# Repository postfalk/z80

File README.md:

## Recent Bring-Up Notes

See [BASIC_DEBUG_2026-04-11.md](./BASIC_DEBUG_2026-04-11.md) for a summary of:

- BASIC workspace/RAM mapping fixes
- toolchain findings (`zasm` vs `z80asm`)
- UART and RAM smoke-test ROMs
- current diagnosis of the remaining BASIC startup issue

#My Z80 Computer

### Assembler software ####

There is a Z80 assembler in the Ubuntu universe repos!!!

```
sudo apt-get install z80asm 
```

Make sure z80asm is in your executable path. There is also a de-assembler for binaries (z80dasm).

I wrote a simple Python script to automate assembly.

```
python assemble.py -i test.asm
```

In order to review binary hex code install bless:

```
sudo apt-get install bless
```

Most software and examples are written in TASM, I found a compatible project still maintained called ZASM

http://k1.spdns.de/Develop/Projects/zasm/Distributions/

CPM setup

This page proved very useful

http://cpuville.com/cpm_on_new_computer.html

(Currently validating its usefulness)

------------- Much of the below is now obsolete ------------------

**Arduino driven Z80 development**

The Arduino is gone now. Development is fun without it. However, the form factor is still there. Arduino could be used for debugging as needed.

~~The basic idea of this project is to use an Arduino to support the development of a z80 computer system and debug any of its components in the process. The Arduino stands in as ...~~

~~a) reset generator~~
~~b) clock~~
~~c) ROM for the lowest 64byte 0000h-003Fh~~

~~The z80 code is fed from a C array to PORTD, PORTB (with 6pins on an Arduino UNO R3) as address bus, and PORTC simulates the control bus (RD --> PIN4, MRQ --> PIN2, RESET <-- PIN3, CLOCK <-- Pin5). The array index correspondends directly with the z80 system address.~~

~~The z80 board is more or less configured as an Arduino shield (even though bigger, the Arduino is plucked in upside down on top of it). In order to run the board without the Arduino, I created a circuit on an Arduino shield PCB with the reset and clock circuit. Thus, it is possible to go back and forth between normal computer operation and running debug code from Arduino.~~

~~The Arduino emulation runs somewhat over 600khz after stripping all pinMode routines out of the Arduino code. (I wonder whether the ```if ... else ...``` control structure could be replaced with bitwise logic as well).~~

~~After Arduino reset, the Aruino code will perform a z80 reset as well (which needs at least 4 clock cycles).~~

~~The clock speed can be modified by nserting Arduino delays in the code which is very useful for debugging. ```Serial.println``` ~~proved also very useful even though it might conflict with z80 data bus on PORT D. For this reason it needs to be placed strategically (e.g. at the high phase of the clock cycle).~~

A new idea is to use the Arduino as a simple IO device at the Z80 bus. At a 4Mhz clock it would require to use the WAIT signal.

***Prerequisites***

***EEPROM***

I got a very cheap, very universal EEPROM programmer called MiniPro TL866xx. It works perfectly with following project: 
Install the project if you want to use this project to directly write XPROMS with the code below.

https://github.com/vdudouyt/

Tested with [XICOR 28C64] (https://www.jameco.com/Jameco/Products/ProdDS/74827.pdf). The python code below assumes this 8k by 8byte device. Change code accordingly for other devices or more flexible use.

Example use:

````sh
minipro -p X28C64 -w d88_rom.bin
````

***RAM***

http://ee-classes.usc.edu/ee459/library/datasheets/628128.pdf

***Current configuration***

The circuit follows very closely http://www.z80.info/gfx/z80test.gif.

Differences: 

- I am using the more original ZILOG z80 PIO.

*Addresses*:

Memory:  

0000h - 003Fh   Arduino ROM emulation  
or  
0000h - 7FFFh   Space for ROM  
8000h - FFFFh   (static) RAM  

I/O:  

00h - 03h   PIO 
  00h         PORT A - ctrl  
  01h         PORT A - data  
  02h         PORT B - ctrl  
  03h         PORT B - data  
80h - 87h   UART - TL16C550A, documentation: http://www.pci-card.com/TL16C550.pdf

Using the 74HCT138 for address decoding we can address 8 devices (2 of the lines are still unused). The wiring is a little bit unusual here: A - A7, B - A6, C - A5

***Example code in this project***

*piobasics.asm*

Just turns bit 0 at port B on if addresses are configured as above. (any speed, originally 1 to 10hz :) )

*pioextended.asm*

Blinks bit 0 at port B if addresses are configured as above (optimized for, i.e. visible at 600kHz clock). Also requires RAM at ffffh for sub routine call. 

*d88.asm*

A somewhat unsuccessful attempt to drive a I2C 8x8 LED display from Adafruit. The program is able to output a "picture". However, the module used requires continous I2C clock which is hard to provide without timer interrupt. Might pick this project up once CTC interupts are available.

*serial.asm*

Basic implementation of a serial communixcation. Minimal working (output) setup using 9600-8-N-1 configuration:

To set the baud rate, we need to access the divisor registers, which is done by setting the most significant bit of the line control register to 1.

- set register 83 to 80 (1000 0000)

- now set dividers:
  
  * set register 80h to 0ch (12 for 9600)

  * set register 81h to 00h 

- now configure line control register

- set register 83h to 03h

- now transmit data by setting value of register 80h

- check register 85h bit 4 will tell whether transmission register is clear

*bootloader.asm*

- load file from serial port

- assembled code needs to start on 0800h

- file end is determined by time out

- jump to start program

*keyboard.asm*

- simple serial reflector of keyboard activity

- load with bootloader

***Documentation Links***

[Zilog User Manual] (http://www.z80.info/zip/z80cpu_um.pdf)

[CPM User Manual](http://www.cpm.z80.de/manuals/cpm3-usr.pdf)

###Explore

http://www.ecstaticlyrics.com/electronics/SPI/fast_z80_interface.html

[CPM 2.2 installation](http://cpuville.com/cpm_on_new_computer.html): This looks pretty reasonable. I like the idea to use an actual IDE hard disk and do not care about its compatibility outside the system. 

[http://www.glynstore.com/content/docs/ftdi/DS_VDIP2.pdf]: Explore this option to get USB sticks and FAT32 going relatively easily and somewhat lame.

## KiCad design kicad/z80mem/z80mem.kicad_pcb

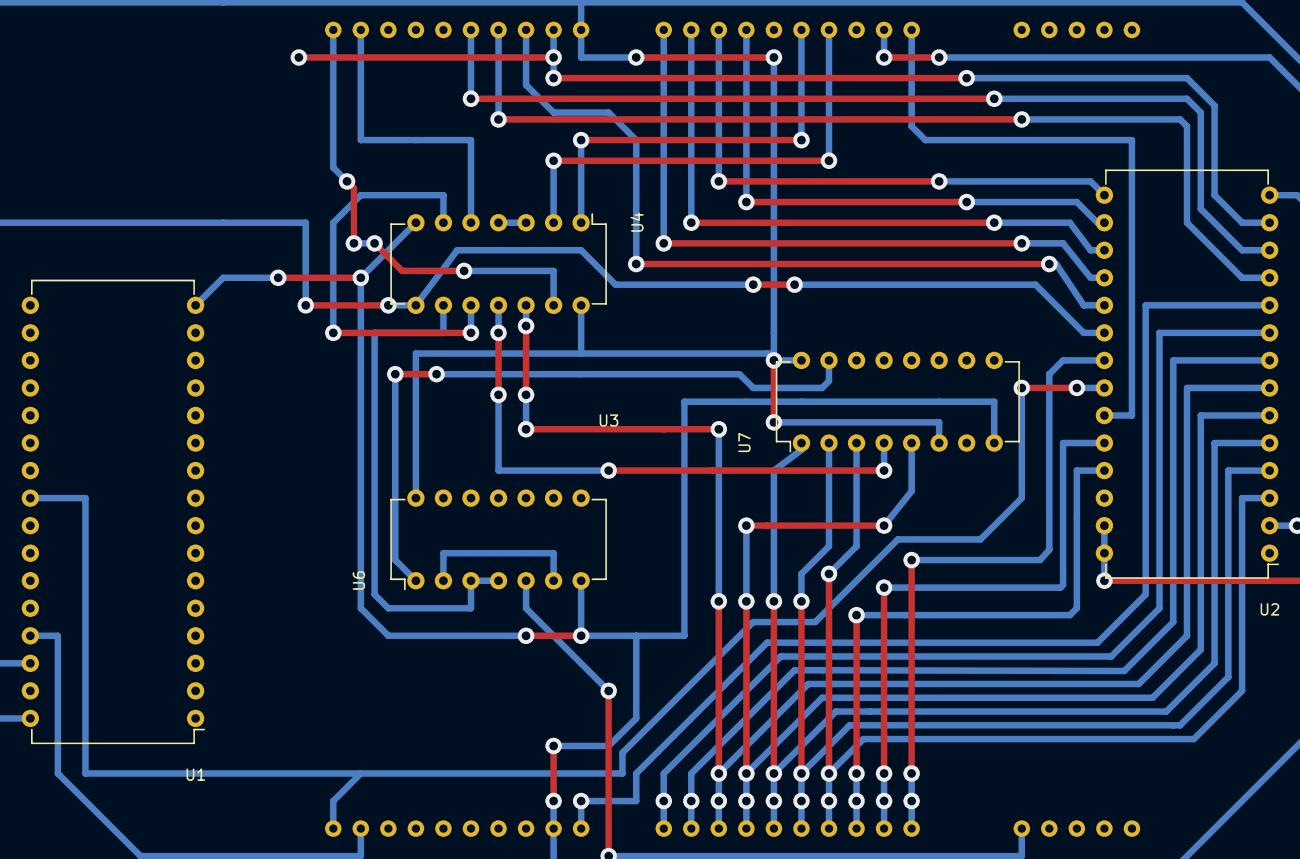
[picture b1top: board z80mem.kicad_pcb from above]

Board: 2 copper layers, 6 parts (0 on the bottom side), 37 nets.

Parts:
U1: MS628128; DIP-32_W15.24mm
U2: 2764; DIP-28_W15.24mm
U3: z80pcb; z80systemboard
U4: 74LS32; DIP-14_W7.62mm
U6: 7400; DIP-14_W7.62mm
U7: 74LS138; DIP-16_W7.62mm

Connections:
GND: U1.16, U2.14, U3.29, U4.7, U6.7, U7.8
unnamed: U1.30, U2.20, U4.8
unnamed: U4.3, U4.4
unnamed: U4.9, U6.3, U6.4
unnamed: U4.6, U4.10
unnamed: U4.11, U7.4
unnamed: U6.1, U7.15
unnamed: U6.2, U6.6
VCC: U1.32, U2.27, U2.28, U3.11, U4.14, U6.14, U7.6, U7.16
a0: U2.10, U3.30
a1: U2.9, U3.31
a2: U2.8, U3.32
a3: U2.7, U3.33, U4.12
a4: U2.6, U3.34, U7.5
a5: U2.5, U3.35, U7.1
a6: U2.4, U3.36, U7.2
a7: U2.3, U3.37, U7.3
a8: U2.25, U3.38
a9: U2.24, U3.39
a10: U2.21, U3.40
a11: U2.23, U3.1
a12: U2.2, U3.2
a14: U3.4, U4.2
a15: U3.5, U4.1
d0: U1.13, U2.11, U3.14
d1: U1.17, U2.12, U3.15
d2: U1.15, U2.13, U3.12
d3: U1.14, U2.15, U3.8
d4: U1.18, U2.16, U3.7
d5: U1.19, U2.17, U3.9
d6: U1.20, U2.18, U3.10
d7: U1.21, U2.19, U3.13
iorq: U3.20, U4.13
mreq: U1.22, U3.19, U4.5
rd: U1.24, U2.22, U3.21
reset: U3.46, U6.5
wr: U1.29, U3.22

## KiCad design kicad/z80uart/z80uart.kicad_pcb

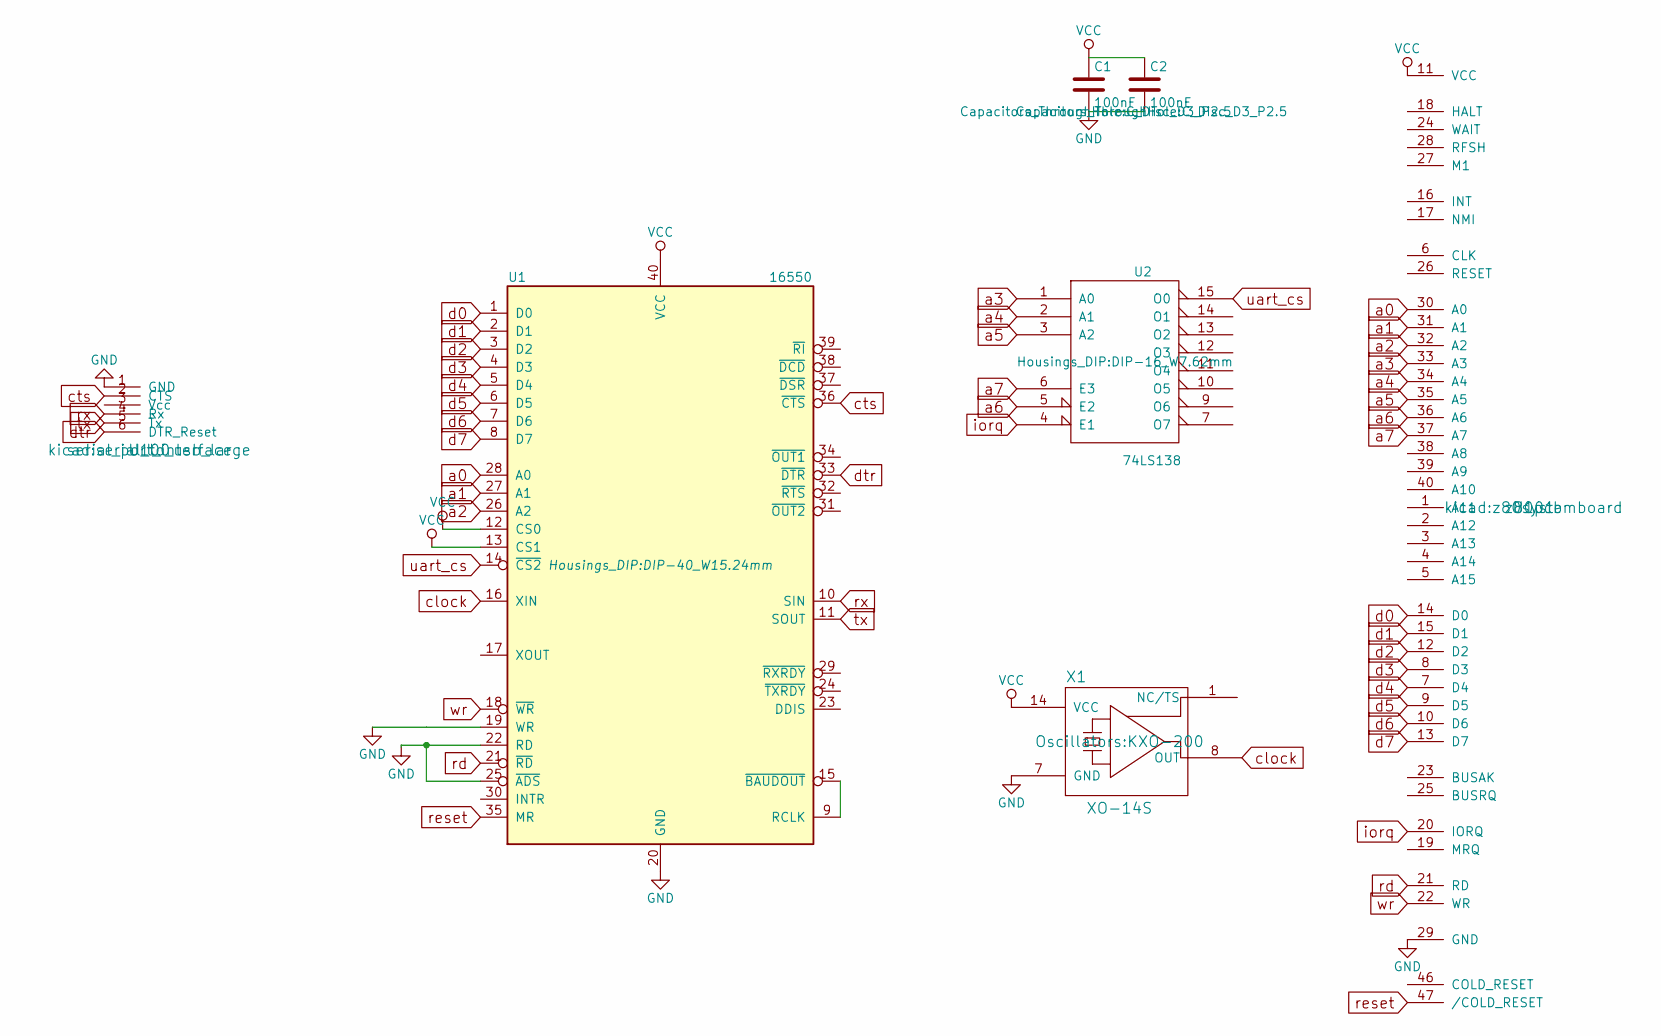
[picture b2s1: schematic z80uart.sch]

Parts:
C1, C2: 100nF; C_Disc_D3_P2.5
U1: 16550; DIP-40_W15.24mm
U2: 74LS138; DIP-16_W7.62mm
U100: serial_port_interface; serial_to_usb_large
U101: z80pcb; z80systemboard
X1: XO-14S; KXO-200

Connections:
unnamed: U1.9 (RCLK), U1.15 (~BAUDOUT~)
a0: U1.28 (A0), U101.30 (A0)
a1: U1.27 (A1), U101.31 (A1)
a2: U1.26 (A2), U101.32 (A2)
a3: U2.1 (A0), U101.33 (A3)
a4: U2.2 (A1), U101.34 (A4)
a5: U2.3 (A2), U101.35 (A5)
a6: U2.5 (E2), U101.36 (A6)
a7: U2.6 (E3), U101.37 (A7)
clock: U1.16 (XIN), X1.8 (OUT)
cts: U1.36 (~CTS~), U100.2 (CTS)
d0: U1.1 (D0), U101.14 (D0)
d1: U1.2 (D1), U101.15 (D1)
d2: U1.3 (D2), U101.12 (D2)
d3: U1.4 (D3), U101.8 (D3)
d4: U1.5 (D4), U101.7 (D4)
d5: U1.6 (D5), U101.9 (D5)
d6: U1.7 (D6), U101.10 (D6)
d7: U1.8 (D7), U101.13 (D7)
dtr: U1.33 (~DTR~), U100.6 (DTR_Reset)
iorq: U2.4 (E1), U101.20 (IORQ)
rd: U1.21 (~RD~), U101.21 (RD)
reset: U1.35 (MR), U101.47 (/COLD_RESET)
rx: U1.10 (SIN), U100.4 (Rx)
tx: U1.11 (SOUT), U100.5 (Tx)
uart_cs: U1.14 (~CS2~), U2.15 (O0)
wr: U1.18 (~WR~), U101.22 (WR)

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
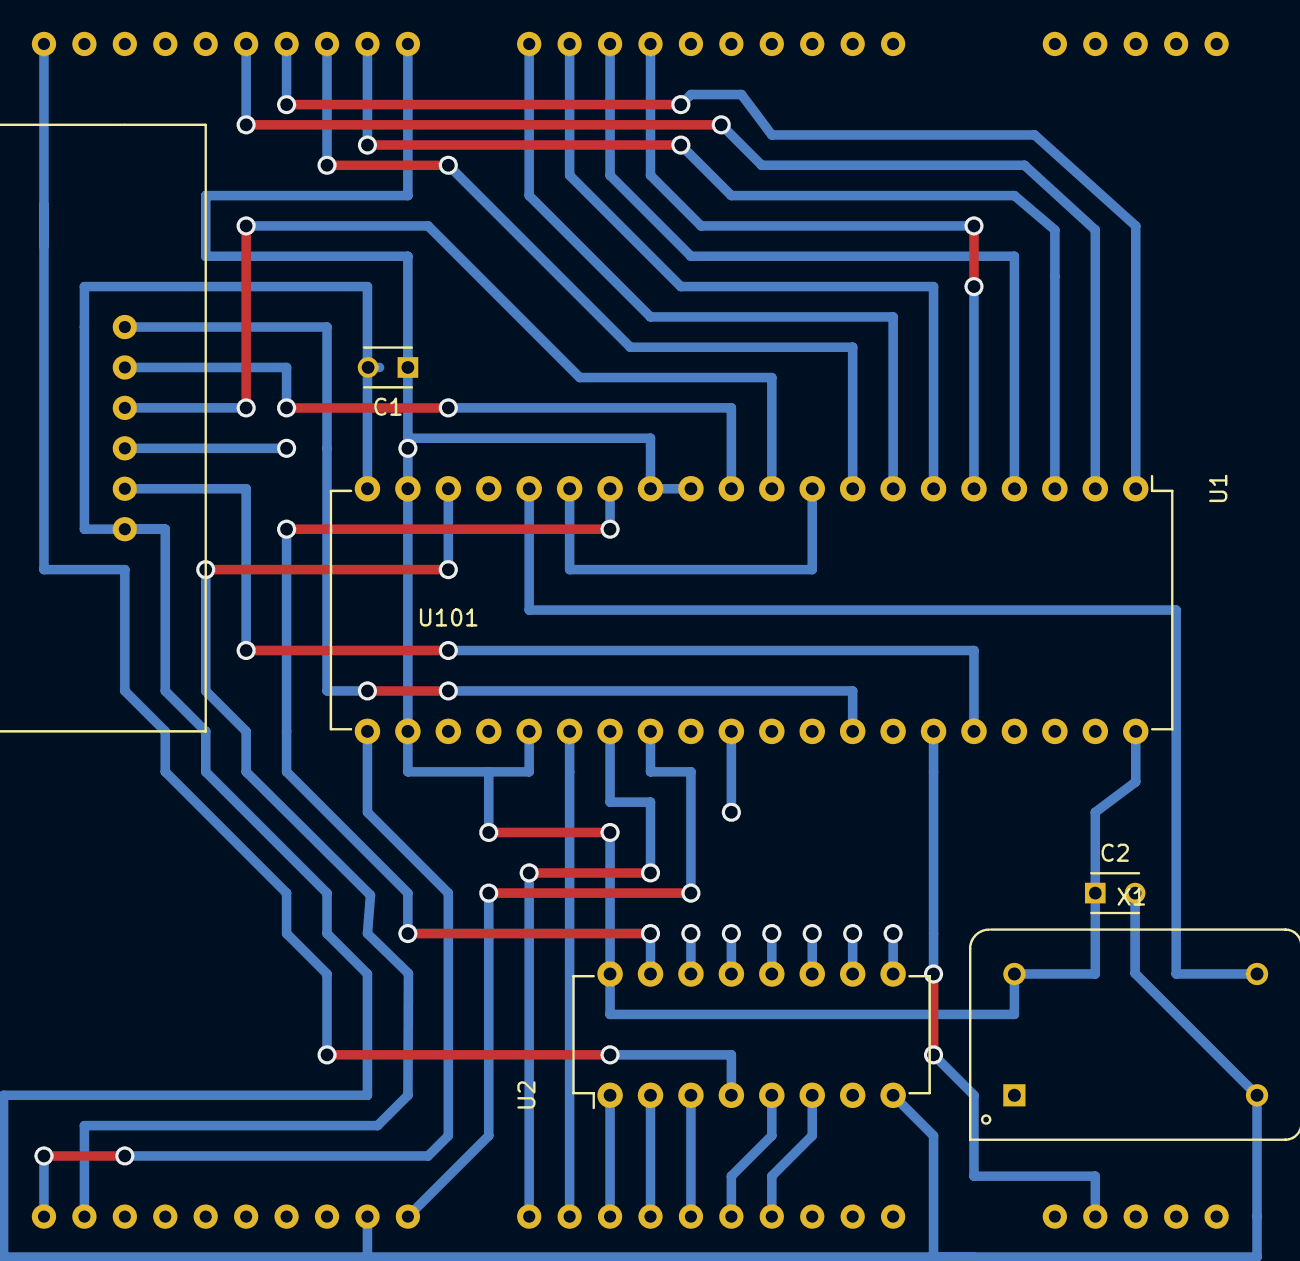
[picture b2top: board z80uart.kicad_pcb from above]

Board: 2 copper layers, 7 parts (0 on the bottom side), 29 nets.

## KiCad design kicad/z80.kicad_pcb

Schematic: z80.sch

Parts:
C1: 100n; C_Disc_D7.5_P5
C2: 47μF; C_Radial_D7.5_L11.2_P2.5
C3: 10μF; C_Radial_D7.5_L11.2_P2.5
D1, D2, D3, D4, D5: LED; LED-5MM
D6, D7: 1N4148; Diode_DO-35_SOD27_Horizontal_RM10
P1: USB_B
R1, R2, R3, R4, R10, R11: 10k; Resistor_Horizontal_RM10mm
R5, R6, R7, R8: 380; Resistor_Horizontal_RM10mm
R9: 680; Resistor_Horizontal_RM10mm
SW1, SW2: SW_PUSH; vintage_reset
U1: Z80CPU; DIP-40_W15.24mm
U2: z80pcb; z80systemboard
U3: 74LS132; DIP-14_W7.62mm
U4: 74LS163; DIP-16_W7.62mm
X1: 16.000Mhz; KXO-200_LargePads

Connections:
CLOCK: U1.6 (~CLK~), U2.6 (CLK), U4.13 (Q1)
GND: C1.2, C2.2, C3.2, D1.1 (K), D2.1 (K), D3.1 (K), D4.1 (K), D5.1 (K), P1.4, SW1.1, SW2.1, U1.29 (GND), U2.29 (GND), U3.7, U4.3 (P0), U4.4 (P1), U4.5 (P2), U4.6 (P3), U4.8 (GND), X1.7 (GND)
unnamed: C2.1, D6.2 (A), R10.2, SW1.2, U3.1
unnamed: C3.1, D7.2 (A), R11.2, SW2.2, U3.2, U3.12, U3.13
unnamed: D1.2 (A), R5.2
unnamed: D2.2 (A), R6.2
unnamed: D3.2 (A), R7.2
unnamed: D4.2 (A), R8.2
unnamed: D5.2 (A), R9.2
unnamed: R1.2, U1.25 (~BUSRQ~), U2.25 (BUSRQ)
unnamed: R2.2, U1.18 (~HALT~), U2.18 (HALT)
unnamed: R3.2, U1.17 (~NMI~), U2.17 (NMI)
unnamed: R4.2, U1.16 (~INT~), U2.16 (INT)
unnamed: R5.1, U1.33 (A3), U2.33 (A3)
unnamed: R6.1, U1.32 (A2), U2.32 (A2)
unnamed: R7.1, U1.31 (A1), U2.31 (A1)
unnamed: R8.1, U1.30 (A0), U2.30 (A0)
unnamed: U1.1 (A11), U2.1 (A11)
unnamed: U1.2 (A12), U2.2 (A12)
unnamed: U1.3 (A13), U2.3 (A13)
unnamed: U1.4 (A14), U2.4 (A14)
unnamed: U1.5 (A15), U2.5 (A15)
unnamed: U1.7 (D4), U2.7 (D4)
unnamed: U1.8 (D3), U2.8 (D3)
unnamed: U1.9 (D5), U2.9 (D5)
unnamed: U1.10 (D6), U2.10 (D6)
unnamed: U1.12 (D2), U2.12 (D2)
unnamed: U1.13 (D7), U2.13 (D7)
unnamed: U1.14 (D0), U2.14 (D0)
unnamed: U1.15 (D1), U2.15 (D1)
unnamed: U1.19 (~MREQ~), U2.19 (MRQ)
unnamed: U1.20 (~IORQ~), U2.20 (IORQ)
unnamed: U1.21 (~RD~), U2.21 (RD)
unnamed: U1.22 (~WR~), U2.22 (WR)
unnamed: U1.23 (~BUSACK~), U2.23 (BUSAK)
unnamed: U1.24 (~WAIT~), U2.24 (WAIT)
unnamed: U1.26 (~RESET~), U2.26 (RESET), U3.6
unnamed: U1.27 (~M1~), U2.27 (M1)
unnamed: U1.28 (~RFSH~), U2.28 (RFSH)
unnamed: U1.34 (A4), U2.34 (A4)
unnamed: U1.35 (A5), U2.35 (A5)
unnamed: U1.36 (A6), U2.36 (A6)
unnamed: U1.37 (A7), U2.37 (A7)
unnamed: U1.38 (A8), U2.38 (A8)
unnamed: U1.39 (A9), U2.39 (A9)
unnamed: U1.40 (A10), U2.40 (A10)
unnamed: U2.46 (COLD_RESET), U3.8
unnamed: U2.47 (/COLD_RESET), U3.9, U3.10, U3.11
unnamed: U3.3, U3.4, U3.5
unnamed: U4.2 (Cp), X1.8 (OUT)
VCC: C1.1, D6.1 (K), D7.1 (K), P1.1, R1.1, R2.1, R3.1, R4.1, R9.1, R10.1, R11.1, U1.11 (VCC), U2.11 (VCC), U3.14, U4.1 (~MR), U4.7 (Cep), U4.9 (~Pe), U4.10 (Cet), U4.16 (VCC), X1.14 (VCC)

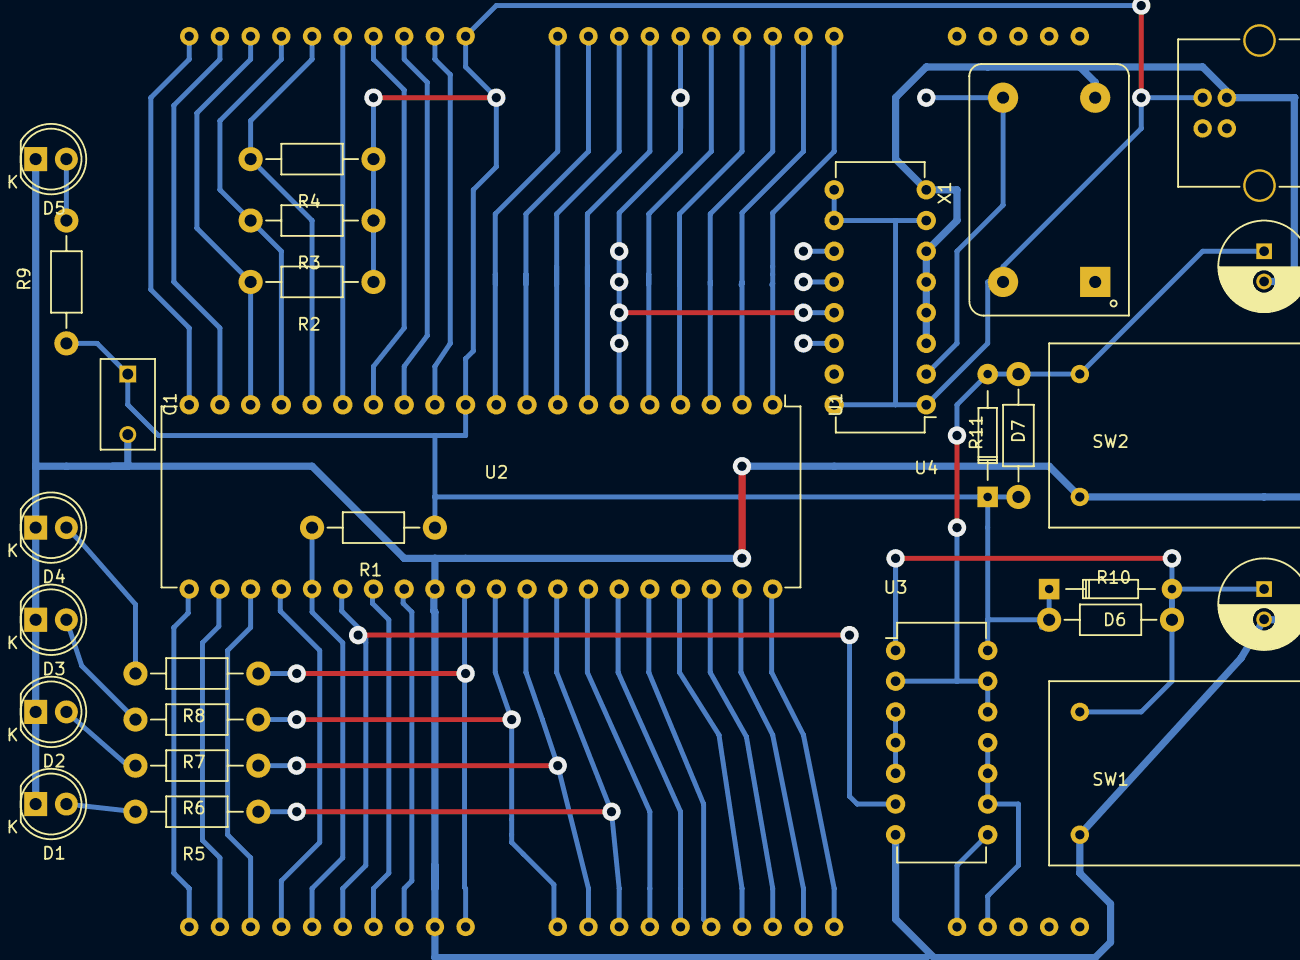
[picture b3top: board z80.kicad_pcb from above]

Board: 2 copper layers, 29 parts (0 on the bottom side), 51 nets.

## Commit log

2015-03-22 implementing basic ROM cycle
2015-03-28 working basic loop
2015-08-09 implement indefinite test loop
2015-08-29 separate z80 code array
2015-10-16 add README
2015-10-16 add python file running pipeline
2015-10-17 completed pipeline
2015-10-17 some cleanup
2015-10-20 add extended pio example
2015-10-23 speeding up Arduino code by factor 15
2015-10-23 add comments
2015-10-23 cleanup python code
2015-10-25 add photo
2015-10-25 additional cleanup, remove debug code
2015-10-25 modularize python code
2015-10-27 make it even better (cleanup)
2015-11-11 first pass on a byte parser
2015-11-11 reset output after byte parse
2015-11-15 parsing and takting works
2015-11-15 add wrapper for futur open drain operation
2015-11-15 exclude compiled c array
2015-11-18 display shows something
2015-11-18 somewhat more stable
2015-11-19 some commentaries
2015-11-20 even simpler
2015-11-20 remove in-memory arguments
2015-11-20 remove redundant command
2015-12-11 remove skip
2016-01-01 still not sure what's going on
2016-01-01 add data loop
2016-01-09 cleanup and renaming
2016-01-09 simplify startTransmission
2016-01-10 get rid of oscillate
2016-01-10 works without oscillate
2016-01-10 structure code
2016-01-18 make sure start condition is long enough
2016-01-18 map data into display raster
2016-01-19 somewhat better still buggy
2016-01-30 fix write_frame
2016-02-22 display finally working
2016-03-03 small simplification
2016-03-19 clean end condition
2016-04-03 first working serial
2016-04-09 add basic serial output implementation
2016-04-09 bootlader: reflect text file
2016-04-12 fix testfile
2016-04-12 simplest bootloader working
2016-04-21 Small serial echo program
2016-04-27 first pass on eagle
2016-05-01 add kicad files
2016-05-03 add reset circuit
2016-05-05 fixed connections
2016-05-31 finish cpu board draft
2016-06-07 add memory card
2016-07-02 add some unfished pcbs
2016-07-02 add simple CPM mem switch test
2016-07-17 add uart
2016-09-03 add UART board
2016-09-03 Add assembler notes to README.md
2016-09-04 add raw files for basic implementation
2016-09-07 basic somewhat working
2016-09-08 add simple memory test
2016-09-10 improved memtest
2016-09-11 improve memorytest
2017-04-29 well al lot of stuff since I committed last time
2026-04-12 fix math
2026-04-12 add AI docs
